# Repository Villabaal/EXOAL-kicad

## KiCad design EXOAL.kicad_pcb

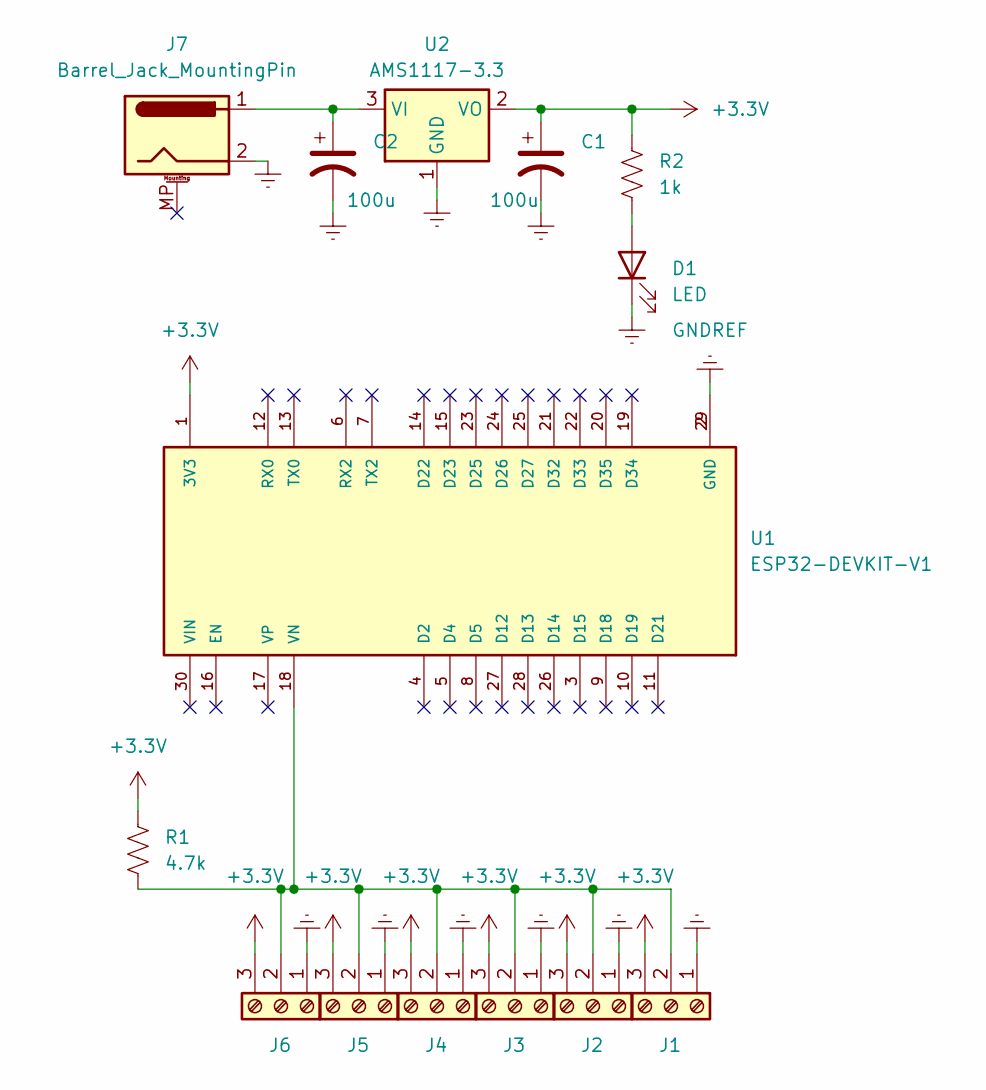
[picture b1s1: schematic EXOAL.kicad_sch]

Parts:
C1, C2: 100u; CP_Radial_D4.0mm_P1.50mm
D1: LED; LED_1206_3216Metric
J1, J2, J3, J4, J5, J6: Screw_Terminal_01x03; TerminalBlock_4Ucon_1x03_P3.50mm_Horizontal
J7: Barrel_Jack_MountingPin; BarrelJack_Horizontal
R1: 4.7k; R_0402_1005Metric
R2: 1k; R_0402_1005Metric
U1: ESP32-DEVKIT-V1; MODULE_ESP32_DEVKIT_V1; PARTREV N/A
U2: AMS1117-3.3; SOT-223-3_TabPin2

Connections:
+3.3V: C1.1, J1.3, J2.3, J3.3, J4.3, J5.3, J6.3, R1.1, R2.1, U1.1 (3V3), U2.2 (VO)
GNDREF: C1.2, C2.2, D1.1 (K), J1.1, J2.1, J3.1, J4.1, J5.1, J6.1, J7.2, U1.2 (GND), U1.29 (GND), U2.1 (GND)
unnamed: D1.2 (A), R2.2
unnamed: J1.2, J2.2, J3.2, J4.2, J5.2, J6.2, R1.2, U1.18 (VN)
unnamed: C2.1, J7.1, U2.3 (VI)

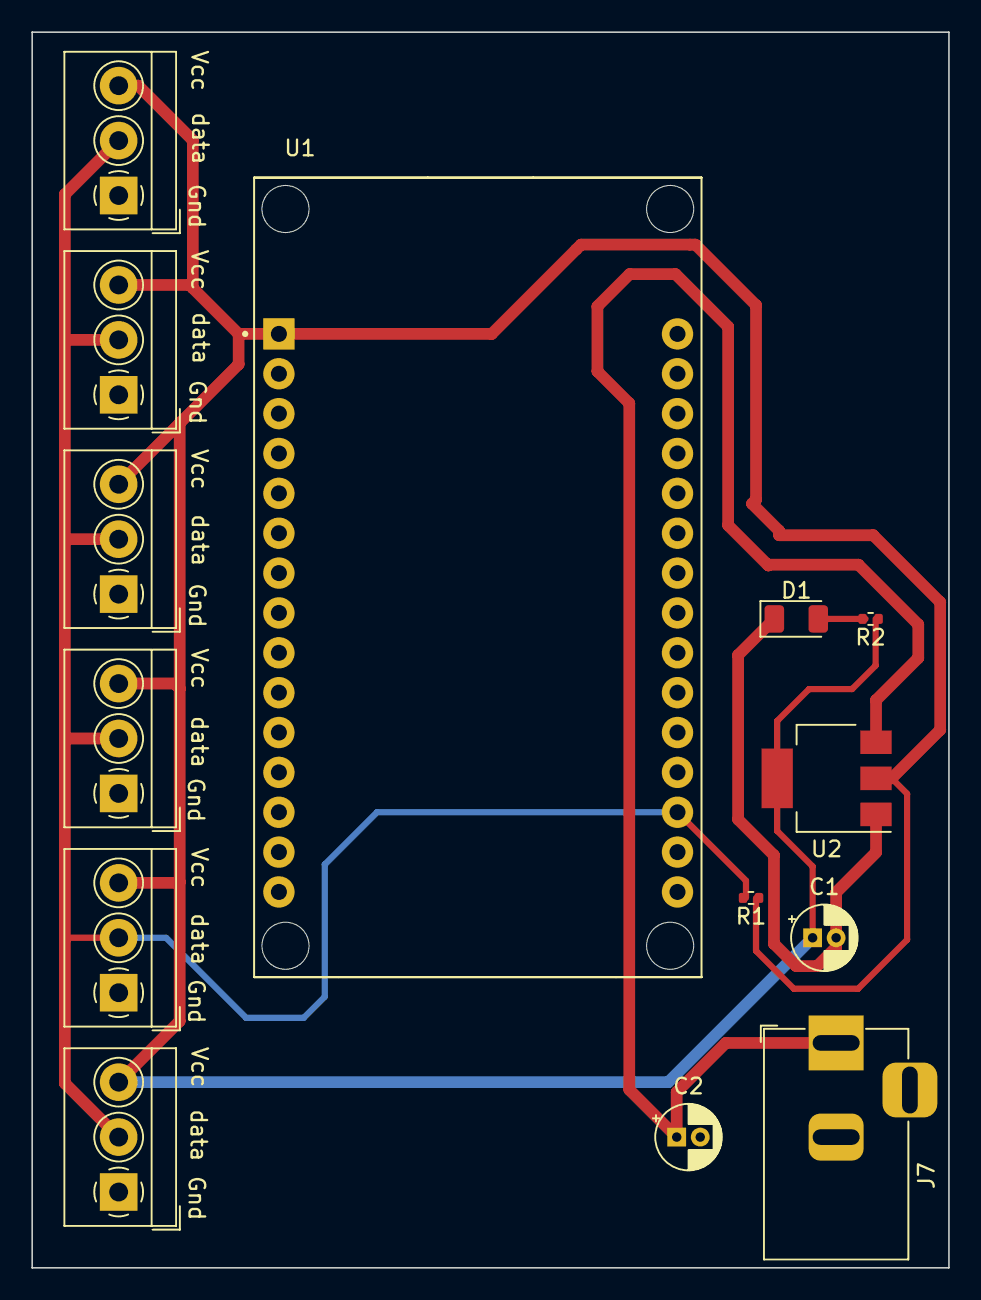
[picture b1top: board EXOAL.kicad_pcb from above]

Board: 2 copper layers, 58.4 x 78.7 mm, 14 parts (0 on the bottom side), 5 nets.

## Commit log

2023-10-06 second commit
